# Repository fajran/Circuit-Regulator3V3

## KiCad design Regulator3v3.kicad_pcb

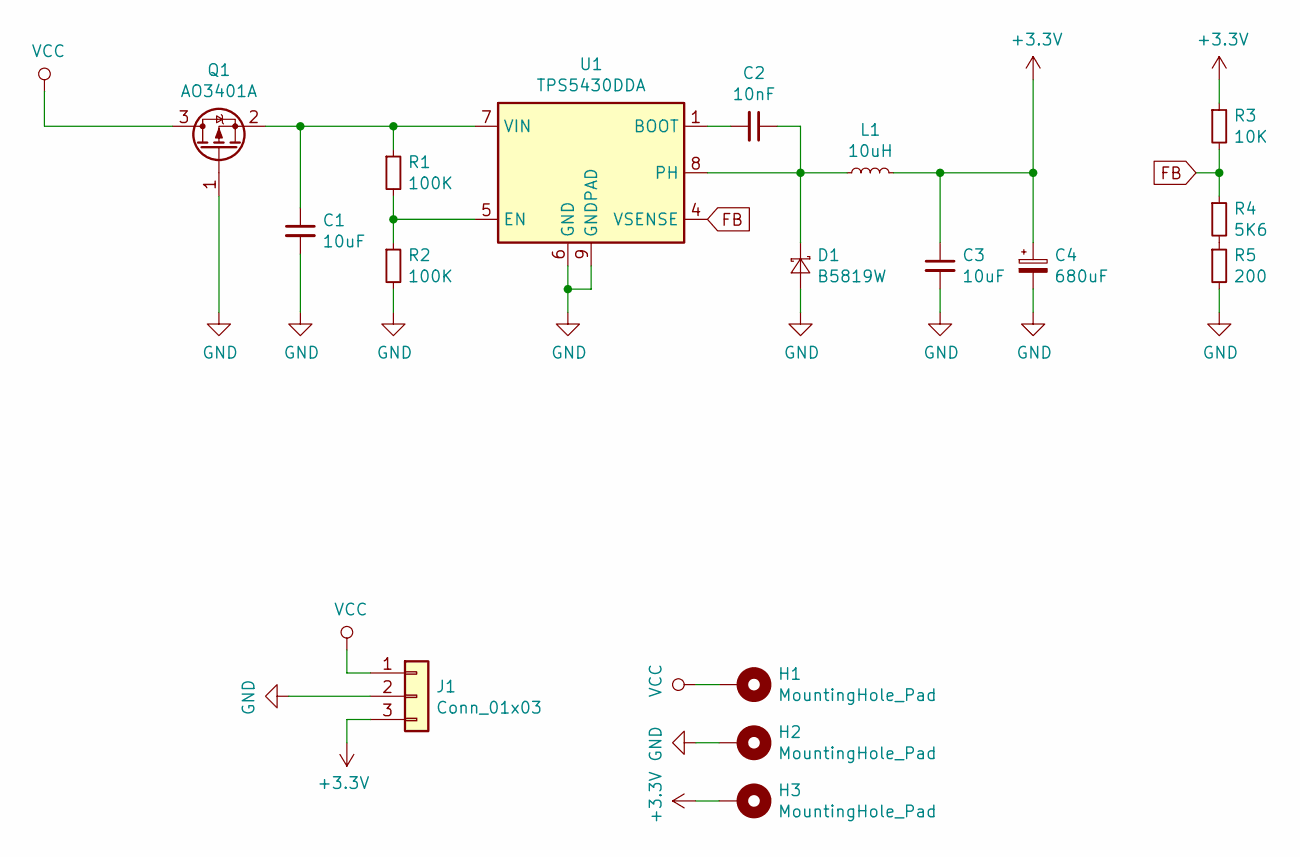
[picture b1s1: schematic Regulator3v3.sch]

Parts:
C1, C3: 10uF; C_1206_3216Metric; LCSC C13585
C2: 10nF; C_1206_3216Metric; LCSC C1846
C4: 680uF; CP_Elec_8x10
D1: B5819W; D_SOD-123; LCSC C8598
H1, H2, H3: MountingHole_Pad; MountingHole_4mm_Pad_Via
J1: Conn_01x03; PinHeader_1x03_P2.54mm_Vertical
L1: 10uH; L_12x12mm_H8mm
Q1: AO3401A; SOT-23; LCSC C15127
R1, R2: 100K; R_1206_3216Metric; LCSC C17928
R3: 10K; R_1206_3216Metric
R4: 5K6; R_1206_3216Metric; LCSC C17928
R5: 200; R_1206_3216Metric; LCSC C17928
U1: TPS5430DDA; TI_SO-PowerPAD-8_ThermalVias

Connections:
+3V3: C3.1, C4.1, H3.1, J1.3, L1.2, R3.1
FB: R3.2, R4.1, U1.4 (VSENSE)
GND: C1.2, C3.2, C4.2, D1.2 (A), H2.1, J1.2, Q1.1 (G), R2.2, R5.2, U1.6 (GND), U1.9 (GNDPAD)
unnamed: C1.1, Q1.2 (S), R1.1, U1.7 (VIN)
unnamed: C2.1, D1.1 (K), L1.1, U1.8 (PH)
unnamed: C2.2, U1.1 (BOOT)
unnamed: R1.2, R2.1, U1.5 (EN)
unnamed: R4.2, R5.1
VCC: H1.1, J1.1, Q1.3 (D)

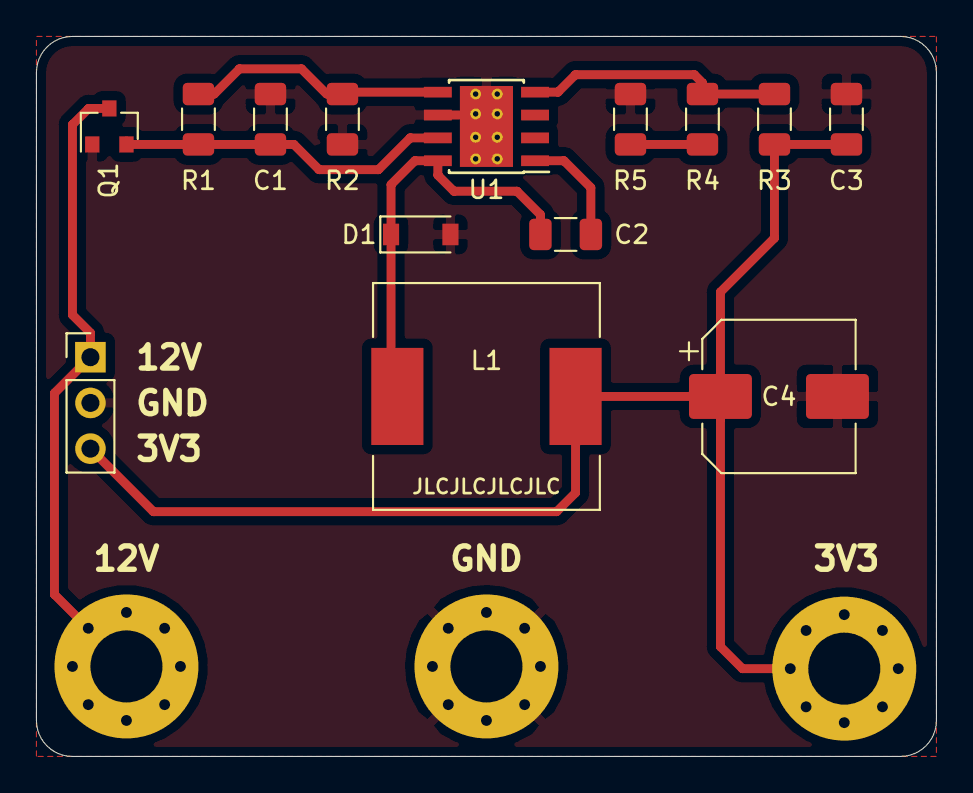
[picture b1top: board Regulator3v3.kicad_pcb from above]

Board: 2 copper layers, 50.0 x 40.0 mm, 17 parts (0 on the bottom side), 9 nets.

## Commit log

2021-08-23 Remove the abandoned mini PCB version
